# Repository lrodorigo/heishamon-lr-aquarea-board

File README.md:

# HeishaMon Aquarea
### Alternative Galvanically Isolated Design

This repository contains an alternative schematic for integrating with Panasonic Aquarea heat pumps using the **HeishaMon** firmware.

## ⚠️ Disclaimer

> This design is **experimental** and has **not yet been tested**.  
> The first hardware version is expected to arrive within a few days.  
> Use at your own risk and feel free to open issues or discussions for feedback and improvements.

## 🛠️ Key Features

- **Galvanically isolated design**  
  Ensures complete electrical isolation from the heat pump for improved safety and reliability.

- **Based on ESP32-C3-DevKitC-02 (official Espressif dev module)**
   
- **Flexible power supply configuration**  
  The board is designed to support different power input scenarios for testing.  
  By default, it uses **12V @ 250mA** to ensure higher available power and better stability.

## 🔧 Firmware Notes

> This board uses different GPIOs than the original HeishaMon design.  
> You **will need to modify the `#define` values** in the firmware source accordingly to match this schematic.  

## 🧩 Usage

The design is tailored for experimenting with various supply options and integration methods, while maintaining full galvanic isolation of the communication lines with the heat pump.

## 📁 Contents

- `export/`: The gerber files

## 📌 Notes

- Intended to be used with HeishaMon firmware (see: https://github.com/Egyras/HeishaMon/)
- Verify jumper settings and isolation components before connecting to the heat pump.

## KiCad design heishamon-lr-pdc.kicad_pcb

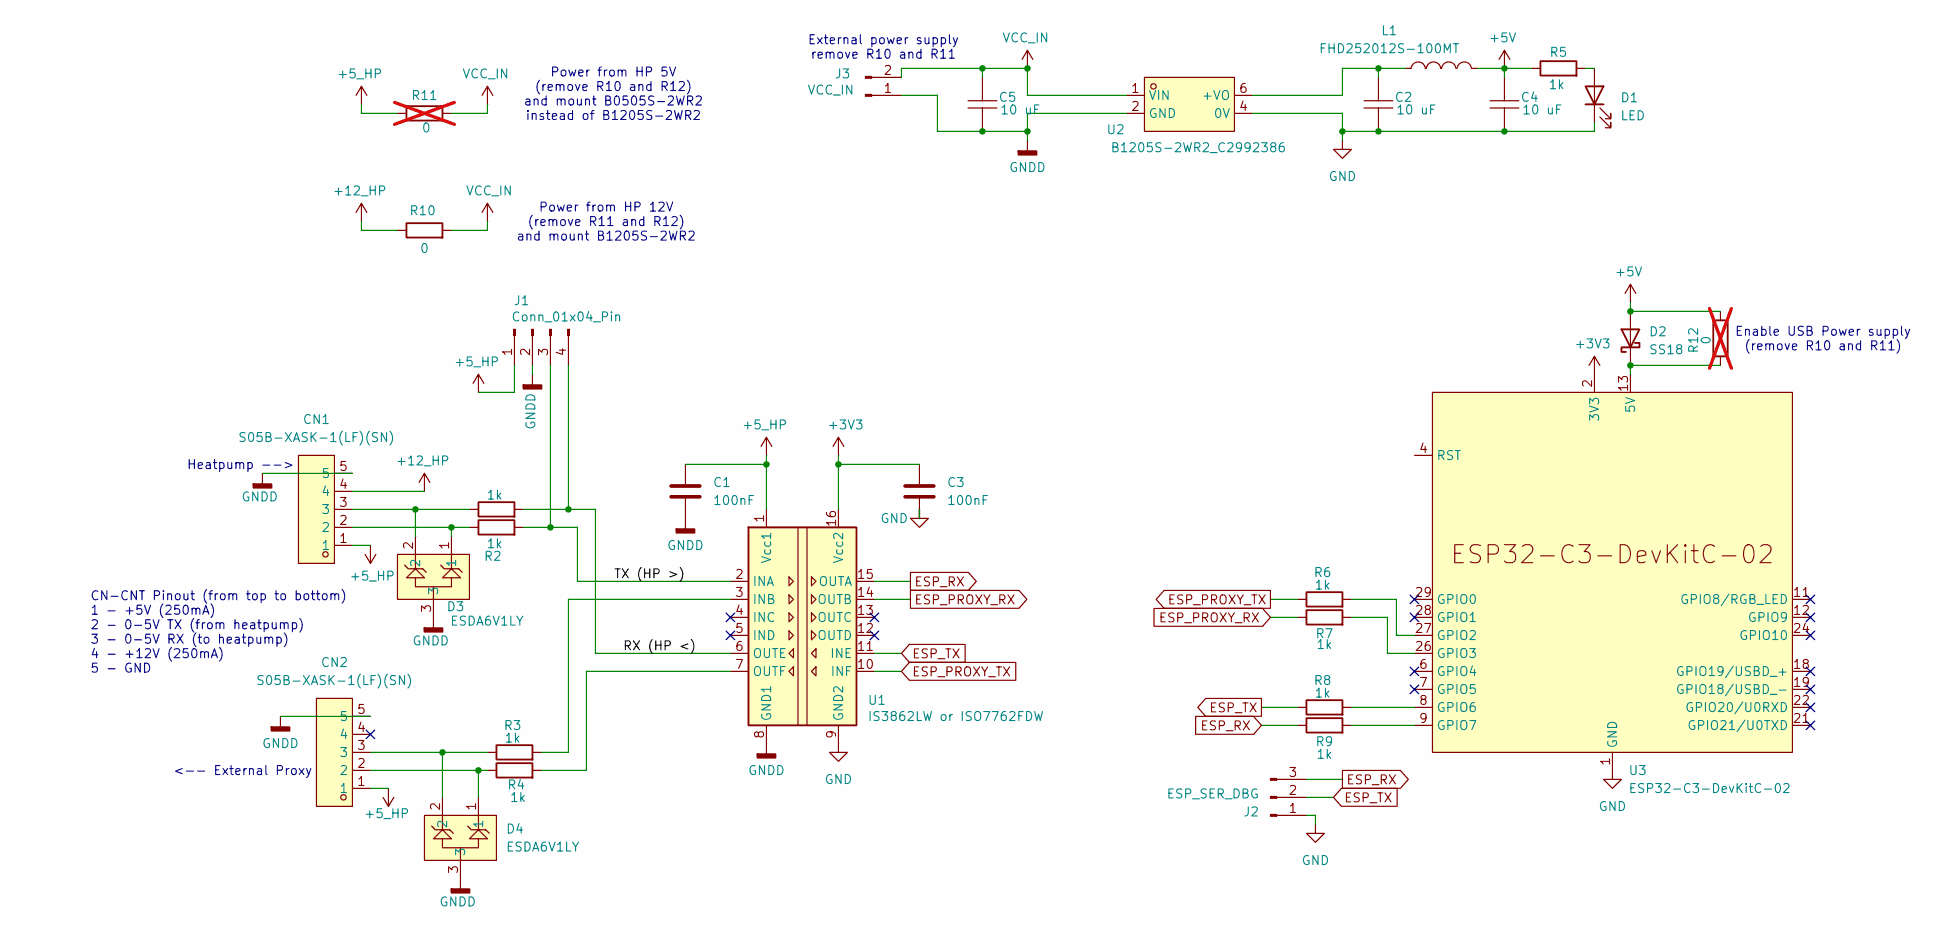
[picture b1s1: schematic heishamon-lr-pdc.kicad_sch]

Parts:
C1, C3: 100nF; C_0805_2012Metric; LCSC C28233
C2, C4, C5: 10 uF; C0805; LCSC Part C15850
CN1, CN2: S05B-XASK-1(LF)(SN); CONN-TH_S05B-XASK-1-LF-SN; LCSC Part C265396
D1: LED; LED_0805_2012Metric
D2: SS18; D_SMA
D3, D4: ESDA6V1LY; SOT-23-3_L2.9-W1.5-P2.0-LS2.5-BR; LCSC Part C2936094
J1: Conn_01x04_Pin; PinHeader_1x04_P2.54mm_Vertical
J2: ESP_SER_DBG; PinHeader_1x03_P2.54mm_Vertical
J3: VCC_IN; PinHeader_1x02_P2.54mm_Vertical; LCSC C2905434
L1: FHD252012S-100MT; IND-SMD_L2.5-W2.0_FHD252012S-6R8MT; LCSC Part C602018
R1, R2, R3, R4, R6, R7, R8, R9: 1k; R_0805_2012Metric; LCSC C17513
R5: 1k; R_0603_1608Metric
R10: 0; R_0805_2012Metric; LCSC C17513
R11, R12: 0; R_0805_2012Metric; LCSC C17513; not fitted
U1: IS3862LW or ISO7762FDW; SOIC-16W_7.5x10.3mm_P1.27mm; LCSC C20598881
U2: B1205S-2WR2_C2992386; PWRM-TH_IBXX05S-2WR3; LCSC Part C2992386
U3: ESP32-C3-DevKitC-02

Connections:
5V: D2.1 (K), R12.1, U3.13 (5V), U3.14 (5V)
+3V3: C3.1, U1.16 (Vcc2), U3.2 (3V3), U3.3 (3V3)
+5V: C4.2, D2.2 (A), L1.2, R5.1, R12.2
+5_HP: C1.1, CN1.1, CN2.1, J1.1, R11.2, U1.1 (Vcc1)
+12_HP: CN1.4, R10.1
/RX (HP <): J1.4, R1.2, U1.6 (OUTE)
/TX (HP >): J1.3, R2.2, U1.2 (INA)
ESP_PROXY_RX: R7.1, U1.14 (OUTB)
ESP_PROXY_TX: R6.1, U1.10 (INF)
ESP_RX: J2.3, R9.1, U1.15 (OUTA)
ESP_TX: J2.2, R8.1, U1.11 (INE)
GND: C2.1, C3.2, C4.1, D1.1 (K), J2.1, U1.9 (GND2), U2.4 (0V), U3.1 (GND), U3.5 (GND), U3.10 (GND), U3.15 (GND), U3.16 (GND), U3.17 (GND), U3.20 (GND), U3.23 (GND), U3.25 (GND), U3.30 (GND)
GNDD: C1.2, C5.1, CN1.5, CN2.5, D3.3, D4.3, J1.2, J3.1, U1.8 (GND1), U2.2 (GND)
unnamed: CN1.2, D3.1, R2.1
unnamed: CN1.3, D3.2, R1.1
unnamed: CN2.2, D4.1, R4.1
unnamed: CN2.3, D4.2, R3.1
unnamed: D1.2 (A), R5.2
unnamed: R3.2, U1.3 (INB)
unnamed: R4.2, U1.7 (OUTF)
unnamed: C2.2, L1.1, U2.6 (+VO)
unnamed: R6.2, U3.27 (GPIO2)
unnamed: R7.2, U3.26 (GPIO3)
unnamed: R8.2, U3.8 (GPIO6)
unnamed: R9.2, U3.9 (GPIO7)
VCC_IN: C5.2, J3.2, R10.2, R11.1, U2.1 (VIN)

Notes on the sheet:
Power from HP 12V (remove R11 and R12) and mount B1205S-2WR2
CN-CNT Pinout (from top to bottom) 1 - +5V (250mA) 2 - 0-5V TX (from heatpump) 3 - 0-5V RX (to heatpump) 4 - +12V (250mA) 5 - GND
Heatpump -->
<-- External Proxy
Enable USB Power supply (remove R10 and R11)
External power supply remove R10 and R11
Power from HP 5V (remove R10 and R12) and mount B0505S-2WR2 instead of B1205S-2WR2

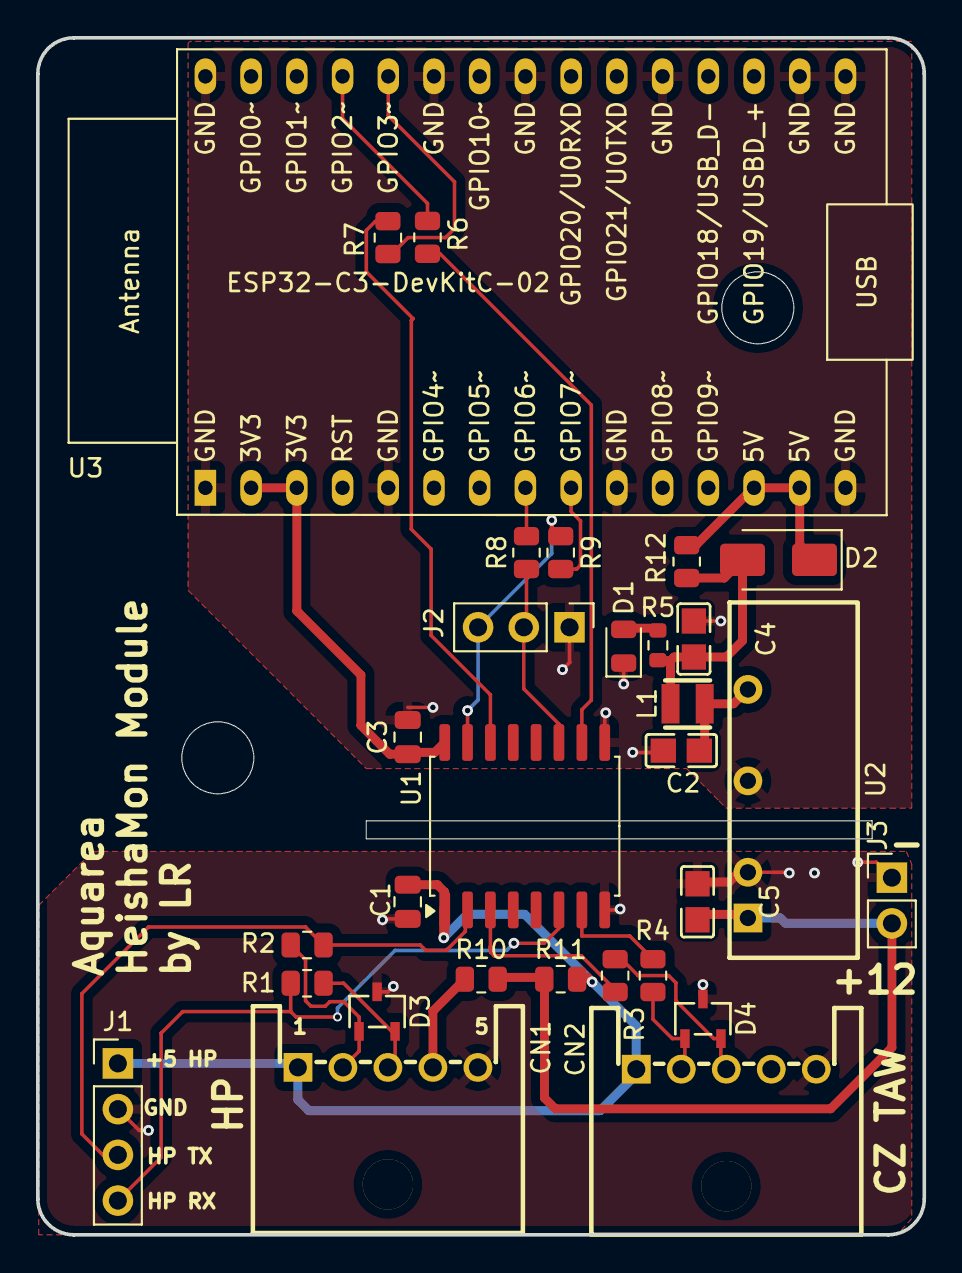
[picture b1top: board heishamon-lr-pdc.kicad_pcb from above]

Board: 2 copper layers, 49.2 x 66.5 mm, 30 parts (0 on the bottom side), 26 nets.

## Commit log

2025-06-05 Img£
